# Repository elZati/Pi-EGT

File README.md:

# Pi-EGT

Marine boat instrument panel for Raspberry Pi 3 with a 5" DSI touchscreen (portrait mode, 480 × 800).

Displays exhaust gas temperature (EGT) in real time via a large circular analog gauge, logs a 15-minute rolling history, monitors ambient temperatures, and — when connected to WiFi — shows today's weather forecast and lightning storm risk.

---

## Hardware

| Component | Detail |
|-----------|--------|
| Raspberry Pi 3 | Any variant |
| Raspberry Pi Touchscreen 2 (5") | DSI, 480 × 800 portrait |
| MAX31855 thermocouple amplifier | EGT sensor via SPI (CE0, 1 MHz) |
| DS18B20 temperature sensor(s) | Up to 2 on 1-Wire bus (GPIO 4) |
| Buzzer | EGT alarm via GPIO 17 (NPN transistor) |
| Custom HAT PCB | LM2596 buck converter from boat battery |

## Features

- **EGT gauge** — circular analog gauge with coloured zone arc (green / amber / red), digital readout and 15-minute scrolling histogram
- **Ambient temperature tiles** — shown automatically when DS18B20 sensors are detected; hidden if sensors disconnect (with 15-second timeout)
- **Buzzer alarm** — activates when EGT exceeds a configurable threshold
- **Weather panel** — today's forecast (icon, description, min/max °C) via [Open-Meteo](https://open-meteo.com/), selectable location
- **Lightning risk panel** — Low / Moderate / High / Active derived from CAPE and WMO weather codes
- **Adaptive poll rate** — 4 Hz normally, drops to 1 Hz if the Pi CPU exceeds 70 °C
- **Portrait layout** — all panels stack vertically; weather and lightning panels are hidden by default and revealed on demand (histogram hides to make room)
- **Setup dialog** — configure EGT gauge min/max, alarm threshold, and mock sensor mode without restarting
- **Fullscreen toggle** — hides the OS taskbar for a clean instrument view
- **Auto-start on boot** via XDG autostart (`~/.config/autostart/pi-egt.desktop`)

## Requirements

```
PyQt5 >= 5.15
requests >= 2.28
spidev >= 3.5      # Pi only
RPi.GPIO >= 0.7    # Pi only
```

Install on the Pi:

```bash
pip3 install -r requirements.txt
```

## Pi OS configuration

Add to `/boot/firmware/config.txt` and reboot:

```ini
dtparam=spi=on        # MAX31855
dtoverlay=w1-gpio     # DS18B20
```

## Running

```bash
cd ~/pi-egt
DISPLAY=:0 python3 main.py            # normal mode
DISPLAY=:0 python3 main.py --mock     # simulated sawtooth sensors
```

Mock mode can also be toggled at runtime from the **Setup** dialog.

## Deployment to Pi

```bash
# Copy project
scp -r . pi@<pi-ip>:~/pi-egt/

# Install desktop shortcut
ssh pi@<pi-ip> "cp ~/pi-egt/pi-egt.desktop ~/Desktop/ && chmod +x ~/Desktop/pi-egt.desktop"

# Install autostart (runs on every boot)
ssh pi@<pi-ip> "mkdir -p ~/.config/autostart && cp ~/pi-egt/pi-egt.desktop ~/.config/autostart/"
```

## Project structure

```
Pi-EGT/
├── main.py                   Entry point; --mock flag; dark Qt palette
├── pi-egt.desktop            Desktop / autostart launcher
├── requirements.txt
├── docs/
│   ├── notes.md              Hardware design notes, PCB, BOM
│   └── software.md           Full software description & architecture
└── pi_egt/
    ├── config.py             Constants and user config (load/save JSON)
    ├── sensors/
    │   ├── max31855.py       SPI thermocouple reader
    │   ├── ds18b20.py        1-Wire temperature reader
    │   └── buzzer.py         GPIO buzzer
    ├── network/
    │   ├── connectivity.py   TCP reachability check
    │   ├── weather.py        Open-Meteo API client
    │   ├── lightning.py      Lightning risk assessment
    │   └── fetch_thread.py   Non-blocking QThread fetch
    └── ui/
        ├── main_window.py    Main window, layout, timers
        └── widgets/
            ├── egt_gauge.py
            ├── histogram.py
            ├── temp_tile.py
            ├── weather_panel.py
            ├── lightning_panel.py
            ├── setup_dialog.py
            └── location_dialog.py
```

## License

MIT

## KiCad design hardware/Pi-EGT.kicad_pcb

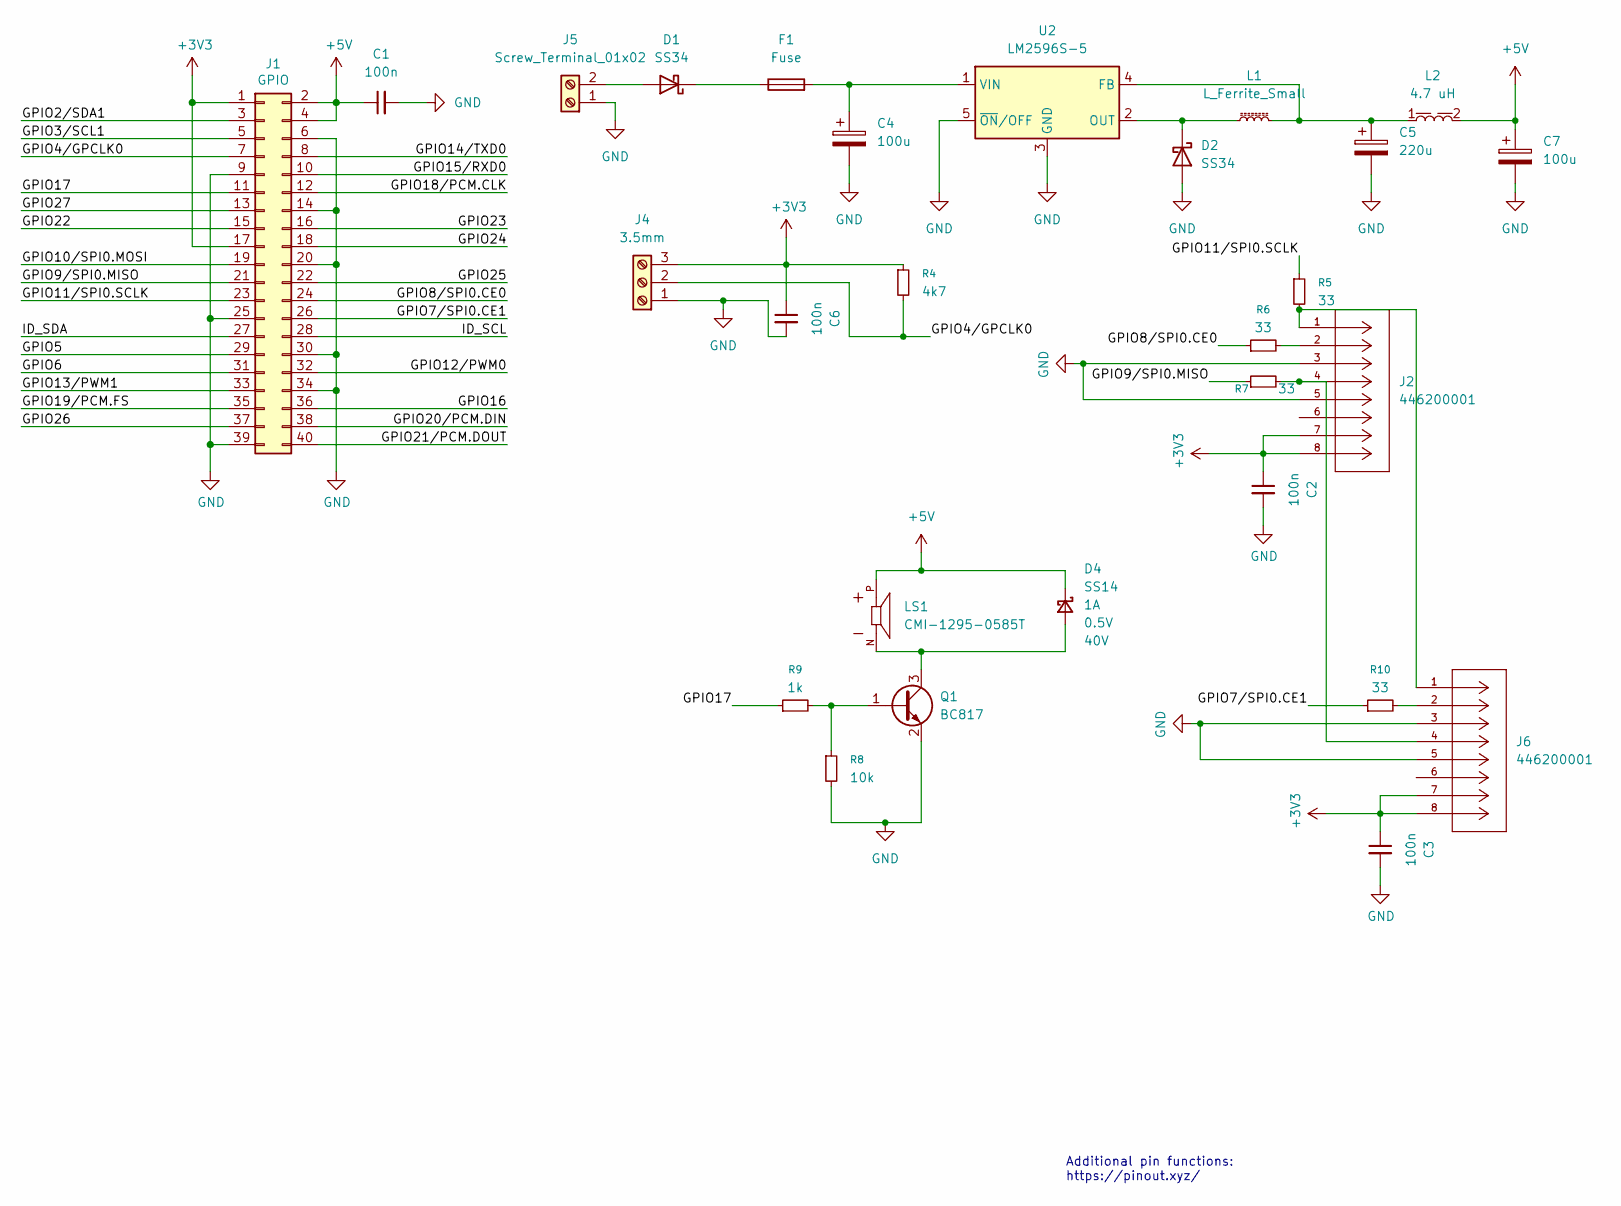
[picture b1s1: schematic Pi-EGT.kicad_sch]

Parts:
C1, C2, C3, C6: 100n; C_0805_2012Metric_Pad1.18x1.45mm_HandSolder; Voltage 1kV; Tolerance 100%
C4, C7: 100u; CP_EIA-7343-20_Kemet-V_HandSolder
C5: 220u; CP_EIA-7343-20_Kemet-V_HandSolder
D1, D2: SS34; D_SMA
D4: SS14; SMA
F1: Fuse; Fuseholder_Blade_Mini_Keystone_3568
J1: GPIO; PinSocket_2x20_P2.54mm_Vertical
J2, J6: 446200001; CON_SD44620_15P75X15P11_MOL; MANUFACTURER_PART_NUMBER 446200001
J4: 3.5mm; TerminalBlock_Phoenix_PT-1,5-3-3.5-H_1x03_P3.50mm_Horizontal
J5: Screw_Terminal_01x02; TerminalBlock_Phoenix_MKDS-3-2-5.08_1x02_P5.08mm_Horizontal
L1: L_Ferrite_Small; L_Bourns_SRR1260
L2: 4.7 uH; L_Wurth_WE-TPC-5828; Part Number 7440530047
LS1: CMI-1295-0585T; CUI_CMI-1295-0585T; PARTREV N/A
Q1: BC817; SOT-23
R4: 4k7; R_0805_2012Metric_Pad1.20x1.40mm_HandSolder
R5, R6, R7, R10: 33; R_0805_2012Metric_Pad1.20x1.40mm_HandSolder
R8: 10k; R_0805_2012Metric_Pad1.20x1.40mm_HandSolder
R9: 1k; R_0805_2012Metric_Pad1.20x1.40mm_HandSolder
U2: LM2596S-5; TO-263-5_TabPin3

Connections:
+3V3: C2.1, C3.1, C6.1, J1.1, J1.17, J2.7, J2.8, J4.3, J6.7, J6.8, R4.1
+5V: C1.1, C7.1, D4.1 (K), J1.2, J1.4, L2.2, LS1.P
/GPIO2/SDA1: J1.3
/GPIO3/SCL1: J1.5
/GPIO4/GPCLK0: J1.7, J4.2, R4.2
/GPIO5: J1.29
/GPIO6: J1.31
/GPIO7/SPI0.CE1: J1.26, R10.1
/GPIO8/SPI0.CE0: J1.24, R6.1
/GPIO9/SPI0.MISO: J1.21, R7.1
/GPIO10/SPI0.MOSI: J1.19
/GPIO11/SPI0.SCLK: J1.23, R5.1
/GPIO12/PWM0: J1.32
/GPIO13/PWM1: J1.33
/GPIO14/TXD0: J1.8
/GPIO15/RXD0: J1.10
/GPIO16: J1.36
/GPIO17: J1.11, R9.1
/GPIO18/PCM.CLK: J1.12
/GPIO19/PCM.FS: J1.35
/GPIO20/PCM.DIN: J1.38
/GPIO21/PCM.DOUT: J1.40
/GPIO22: J1.15
/GPIO23: J1.16
/GPIO24: J1.18
/GPIO25: J1.22
/GPIO26: J1.37
/GPIO27: J1.13
/ID_SCL: J1.28
/ID_SDA: J1.27
GND: C1.2, C2.2, C3.2, C4.2, C5.2, C6.2, C7.2, D2.2 (A), J1.6, J1.9, J1.14, J1.20, J1.25, J1.30, J1.34, J1.39, J2.3, J2.5, J4.1, J5.1, J6.3, J6.5, Q1.2 (E), R8.2, U2.3 (GND), U2.5 (~ON/OFF)
unnamed: D1.2 (A), J5.2
unnamed: D1.1 (K), F1.1
unnamed: D2.1 (K), L1.1, U2.2 (OUT)
unnamed: D4.2 (A), LS1.N, Q1.3 (C)
unnamed: J2.1, J6.1, R5.2
unnamed: J2.2, R6.2
unnamed: J2.4, J6.4, R7.2
unnamed: J6.2, R10.2
unnamed: Q1.1 (B), R8.1, R9.2
unnamed: C5.1, L1.2, L2.1, U2.4 (FB)
unnamed: C4.1, F1.2, U2.1 (VIN)

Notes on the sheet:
Additional pin functions: https://pinout.xyz/

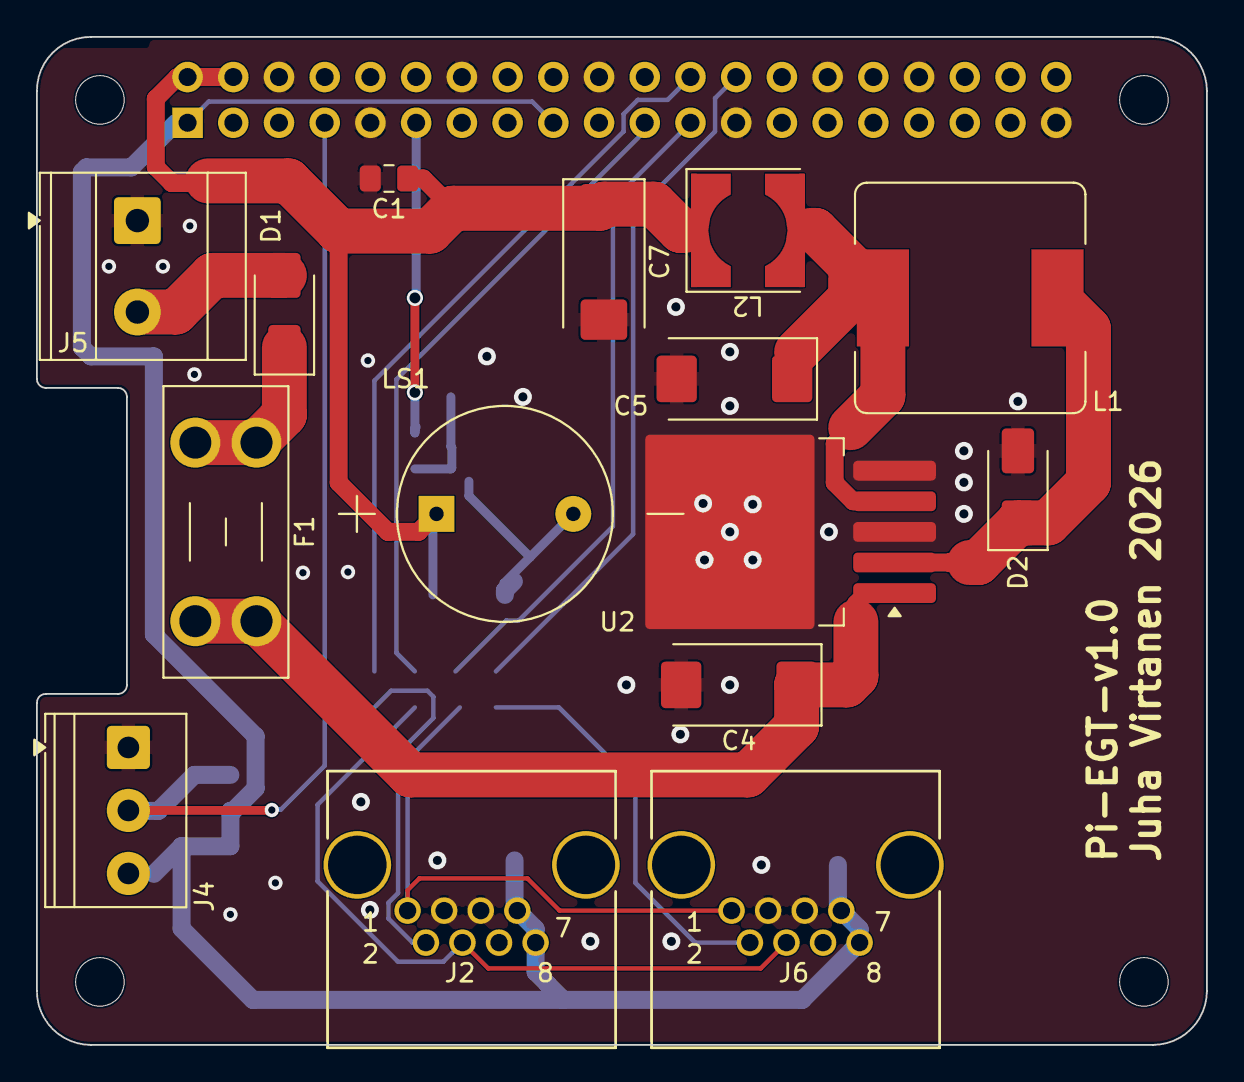
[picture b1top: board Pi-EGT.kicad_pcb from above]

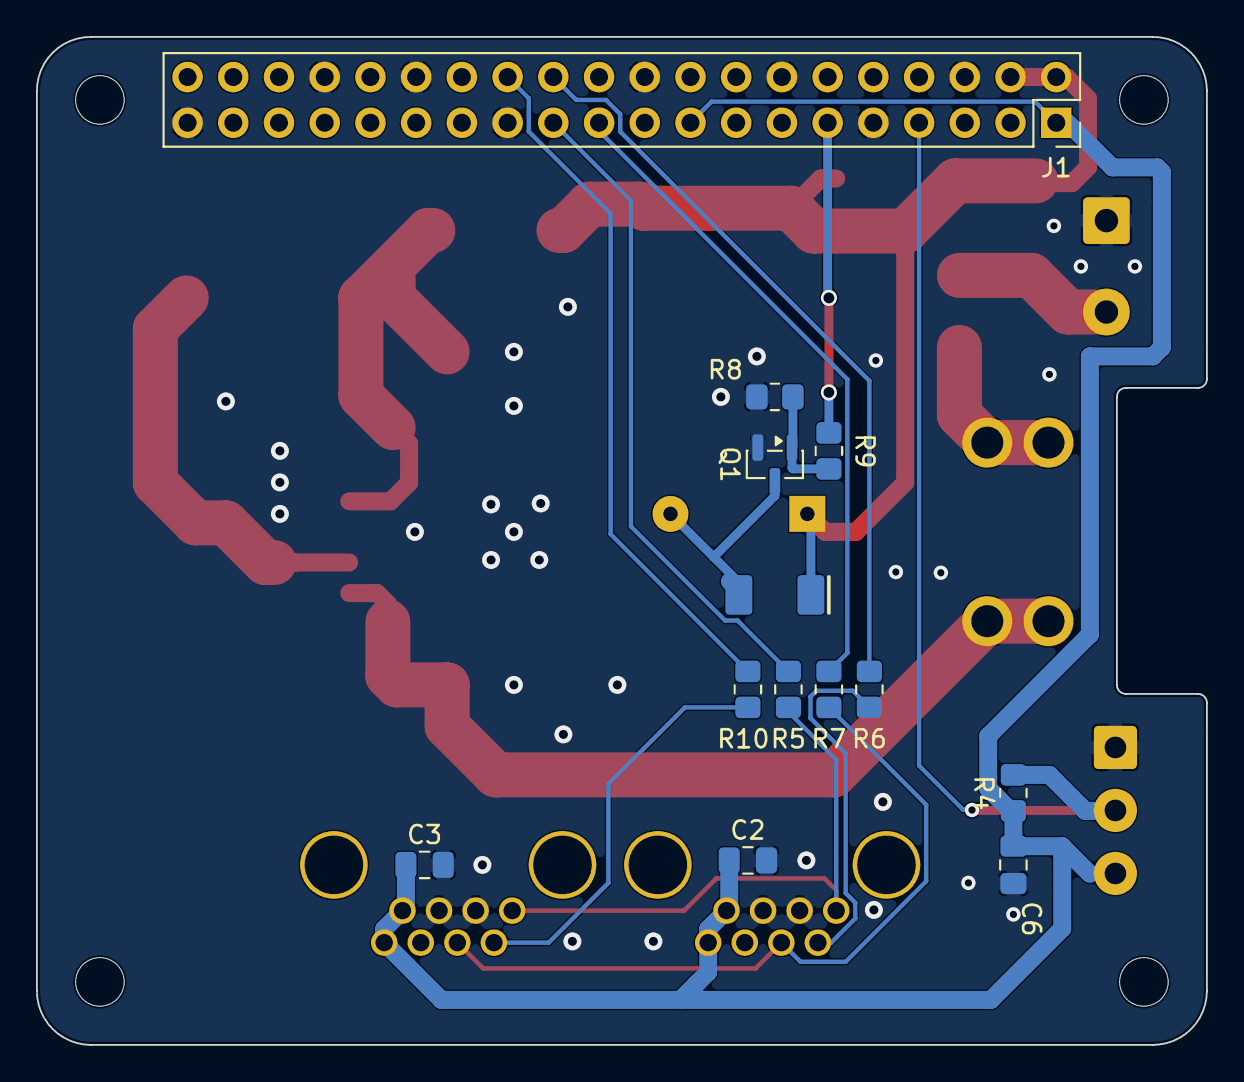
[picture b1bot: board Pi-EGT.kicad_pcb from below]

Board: 2 copper layers, 65.0 x 56.0 mm, 32 parts (13 on the bottom side), 20 nets.

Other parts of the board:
MH1, MH2, MH3, MH4: MountingHole_2.7mm_M2.5
